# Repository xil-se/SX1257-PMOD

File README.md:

# SX1257 PMOD

This is a PMOD built around the SX1257 transceiver. It uses an I2C-SPI bridge (SC18IS602B) since only 8 io pins are used.

RevA Pin-out:
- 1: I2C SCL
- 2: I2C SDA
- 3: CLK_IN (32 or 36 MHz)
- 4: CLK_OUT (36 MHz)
- 5: I_IN
- 6: Q_IN
- 7: Q_OUT
- 8: I_OUT

## RevA errata
- Change crystal footprint.
- Add 2k pull-ups on i2c scl and sda.
- Maybe swap pin 7 and 8, makese sense to keep in and out symmetric.

# RevB

RevB Pin-out:
- 1: I_IN
- 2: Q_IN
- 3: Q_OUT
- 4: I_OUT
- 5: I2C SCL
- 6: I2C SDA
- 7: CLK_IN (32 or 36 MHz)
- 8: CLK_OUT (36 MHz)

## RevB errata

The pins VR_PA, VR_DIG, VR_ANA1 and VR_ANA2 should *not* be tied to VBAT/VCC, which they are. These are pins for decoupling for the internal voltage regulators, i.e. they should *only* be connected to single decoupling capacitors as stated in the datasheet.

- VR_PA: 10nF
- VR_DIG: 100nF
- VR_ANA1: 100nF
- VR_ANA2: 100nF

RX performance is poor. Why? Maybe related to the above, or bad matching circuit?

In the build of 10 units, 2 failed completely and 2 had very bad RX performance. Maybe related to the issue above.

## Changes for RevC / TODO:

- [x] Fix SX1257 Vreg decoupling issue. Done in [#1][i1] / 176024d
- [x] Change to 0402 components. Done in [#1][i1] / 176024d
- [x] Add optional SI514 I2C-programmable oscillator.

[i1]: https://github.com/xil-se/SX1257-PMOD/pull/1

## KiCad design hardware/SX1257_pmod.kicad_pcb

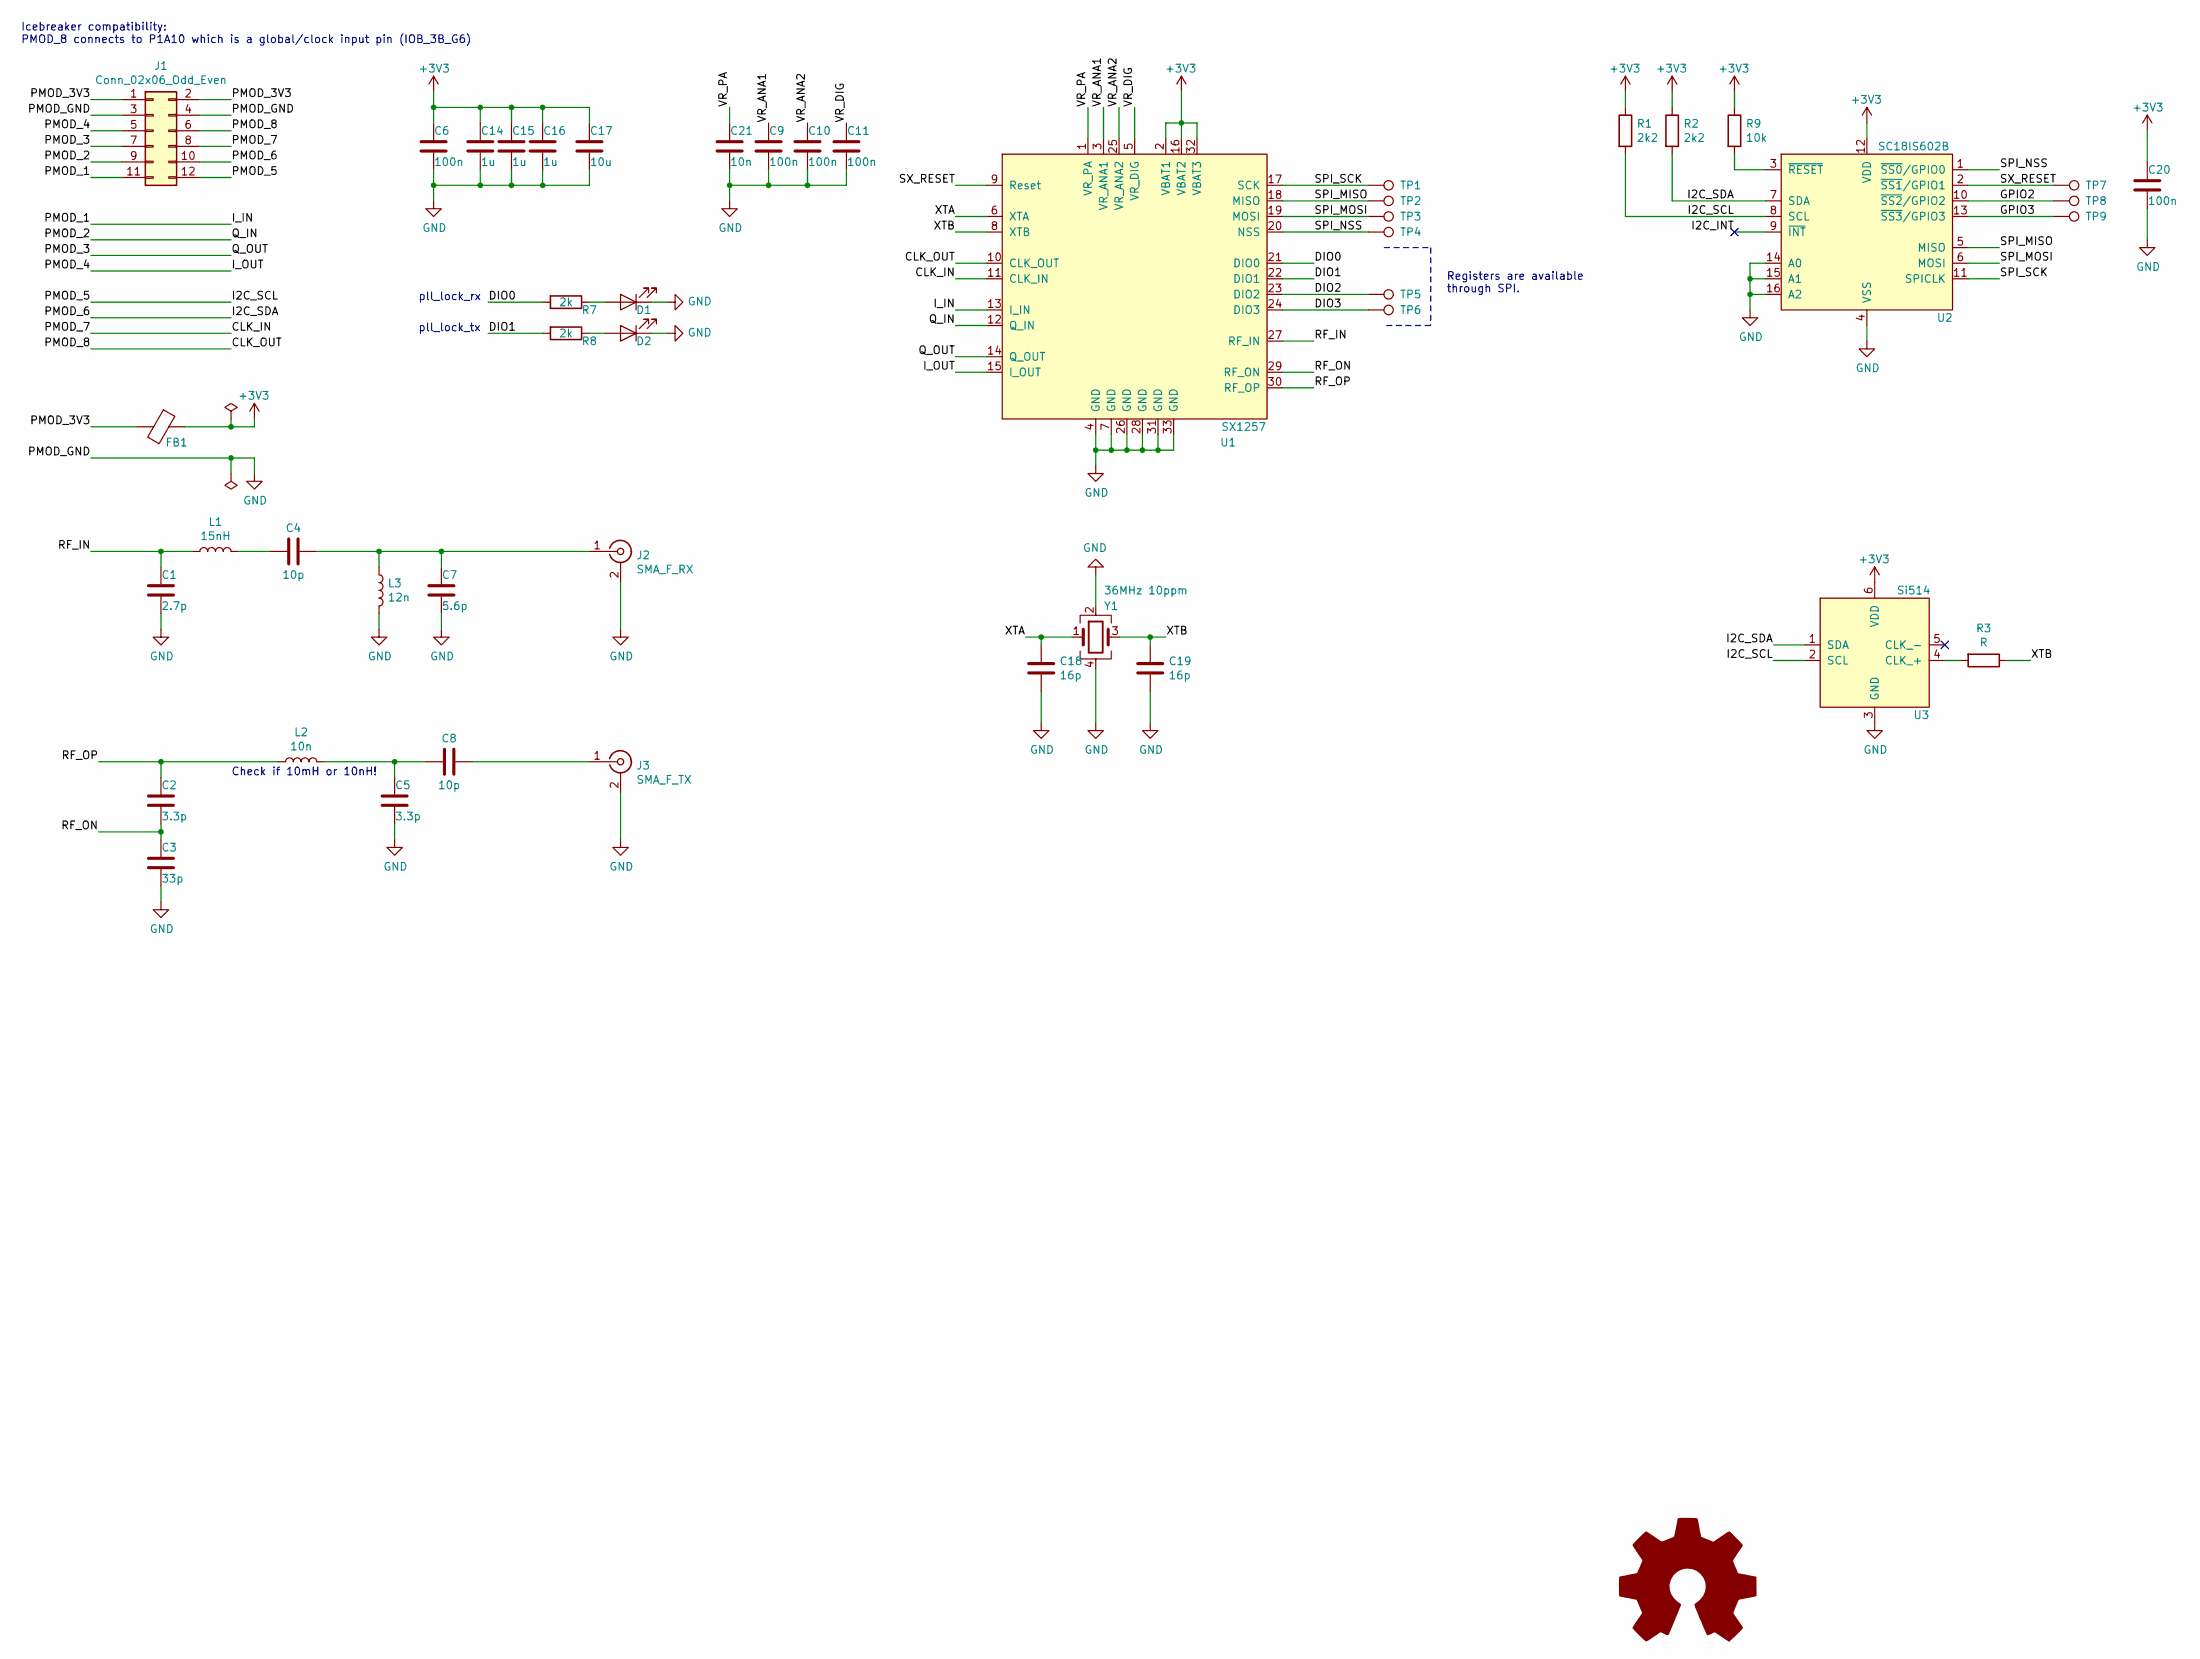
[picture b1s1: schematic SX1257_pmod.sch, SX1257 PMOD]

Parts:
C1: 2.7p; C_0402_1005Metric
C2, C5: 3.3p; C_0402_1005Metric
C3: 33p; C_0402_1005Metric
C4, C8: 10p; C_0402_1005Metric
C6, C9, C10, C11, C20: 100n; C_0402_1005Metric
C7: 5.6p; C_0402_1005Metric
C14, C15, C16: 1u; C_0402_1005Metric
C17: 10u; C_0603_1608Metric
C18, C19: 16p; C_0402_1005Metric
C21: 10n; C_0402_1005Metric
D1, D2: LED; LED_0603_1608Metric
FB1: Ferrite_Bead; L_0603_1608Metric
J1: Conn_02x06_Odd_Even; PinHeader_2x06_P2.54mm_Horizontal
J2: SMA_F_RX; CON-SMA-EDGE; Mouser 960-EMPCB.SMAFSTJBHT
J3: SMA_F_TX; CON-SMA-EDGE; Mouser 960-EMPCB.SMAFSTJBHT
L1: 15nH; L_0402_1005Metric
L2: 10n; L_0402_1005Metric
L3: 12n; L_0402_1005Metric
LOGO1: Logo_Open_Hardware_Large; oshw_logo
R1, R2: 2k2; R_0402_1005Metric
R3: R; R_0402_1005Metric
R7, R8: 2k; R_0402_1005Metric
R9: 10k; R_0402_1005Metric
TP1, TP2, TP3, TP4, TP5, TP6, TP7, TP8, TP9: TestPoint; TestPoint_Pad_D1.0mm
U1: SX1257; QFN-32-1EP_5x5mm_P0.5mm_EP3.1x3.1mm_ThermalVias
U2: SC18IS602B; TSSOP-16_4.4x5mm_P0.65mm
U3: Si514; Oscillator_SMD_Silicon_Labs_3.2x5.0mm_P1.27mm-6pin_5.0x3.2mm
Y1: 36MHz 10ppm; Crystal_SMD_1612-4Pin_1.6x1.2mm; Mouser 815-12W36-6B1UT

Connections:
+3V3: C6.1, C14.1, C15.1, C16.1, C17.1, C20.1, FB1.1, R1.1, R2.1, R9.1, U1.2 (VBAT1), U1.16 (VBAT2), U1.32 (VBAT3), U2.12 (VDD), U3.6 (VDD)
/CLK_IN: J1.8, U1.11 (CLK_IN)
/CLK_OUT: J1.6, U1.10 (CLK_OUT)
/DIO0: R7.2, U1.21 (DIO0)
/DIO1: R8.2, U1.22 (DIO1)
/DIO2: TP5.1, U1.23 (DIO2)
/DIO3: TP6.1, U1.24 (DIO3)
/GPIO2: TP8.1, U2.10 (~SS2~/GPIO2)
/GPIO3: TP9.1, U2.13 (~SS3~/GPIO3)
/I2C_INT: U2.9 (~INT~)
/I2C_SCL: J1.12, R1.2, U2.8 (SCL), U3.2 (SCL)
/I2C_SDA: J1.10, R2.2, U2.7 (SDA), U3.1 (SDA)
/I_IN: J1.11, U1.13 (I_IN)
/I_OUT: J1.5, U1.15 (I_OUT)
/PMOD_2: J1.9, U1.12 (Q_IN)
/PMOD_3: J1.7, U1.14 (Q_OUT)
/PMOD_3V3: FB1.2, J1.1, J1.2
/RF_IN: C1.1, L1.1, U1.27 (RF_IN)
/RF_ON: C2.2, C3.1, U1.29 (RF_ON)
/RF_OP: C2.1, L2.1, U1.30 (RF_OP)
/SPI_MISO: TP2.1, U1.18 (MISO), U2.5 (MISO)
/SPI_MOSI: TP3.1, U1.19 (MOSI), U2.6 (MOSI)
/SPI_NSS: TP4.1, U1.20 (NSS), U2.1 (~SS0~/GPIO0)
/SPI_SCK: TP1.1, U1.17 (SCK), U2.11 (SPICLK)
/SX_RESET: TP7.1, U1.9 (Reset), U2.2 (~SS1~/GPIO1)
/VR_ANA1: C9.1, U1.3 (VR_ANA1)
/VR_ANA2: C10.1, U1.25 (VR_ANA2)
/VR_DIG: C11.1, U1.5 (VR_DIG)
/VR_PA: C21.1, U1.1 (VR_PA)
/XTA: C18.1, U1.6 (XTA), Y1.1
/XTB: C19.1, R3.1, U1.8 (XTB), Y1.3
GND: C1.2, C3.2, C5.2, C6.2, C7.2, C9.2, C10.2, C11.2, C14.2, C15.2, C16.2, C17.2, C18.2, C19.2, C20.2, C21.2, D1.1 (K), D2.1 (K), J1.3, J1.4, J2.2 (Ext), J3.2 (Ext), L3.2, U1.4 (GND), U1.7 (GND), U1.26 (GND), U1.28 (GND), U1.31 (GND), U1.33 (GND), U2.4 (VSS), U2.14 (A0), U2.15 (A1), U2.16 (A2), U3.3 (GND), Y1.2, Y1.4
unnamed: C4.1, C7.1, J2.1 (In), L3.1
unnamed: C4.2, L1.2
unnamed: C5.1, C8.2, L2.2
unnamed: C8.1, J3.1 (In)
unnamed: D1.2 (A), R7.1
unnamed: D2.2 (A), R8.1
unnamed: R3.2, U3.4 (CLK_+)
unnamed: R9.2, U2.3 (~RESET~)

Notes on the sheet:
Check if 10mH or 10nH!
Registers are available through SPI.
Icebreaker compatibility: PMOD_8 connects to P1A10 which is a global/clock input pin (IOB_3B_G6)
pll_lock_rx
pll_lock_tx

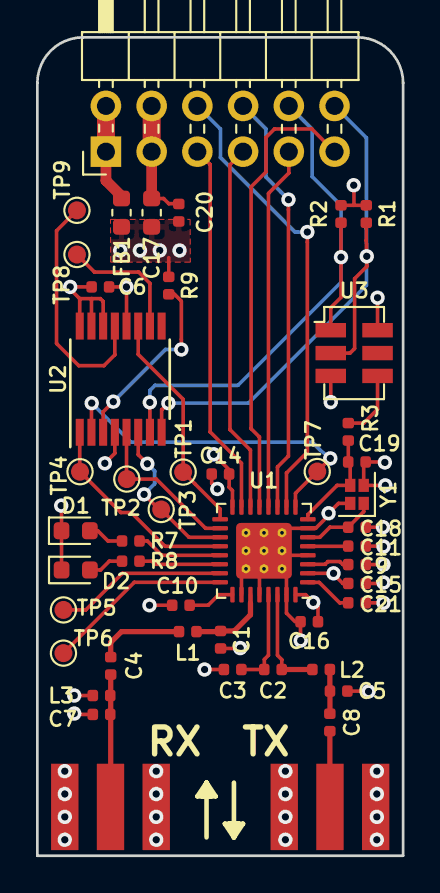
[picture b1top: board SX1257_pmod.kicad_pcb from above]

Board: 4 copper layers, 20.3 x 45.5 mm, 48 parts (1 on the bottom side), 39 nets.

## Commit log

2018-12-31 Initial kicad project
2018-12-31 Add schematic symbol
2019-01-03 Added some caps etc
2019-01-04 Finalized the schematic
2019-01-04 Remove CLK_OUT 0R and tidy up a bit.
2019-01-04 Fix incorrect value of C11 33p => 3.3p
2019-01-04 Change clock
2019-01-04 Add datasheet
2019-01-04 Initial PCB routing
2019-01-05 Fix typo
2019-01-05 Some improvements and pcb work
    - Connected gpio1 to SX_RESET
    - Removed R0 for CLK select
2019-01-05 New pdf
2019-01-06 PCB design almost done.
2019-01-06 Final touches of the pcb
2019-01-06 RevA: Minor changes and produce gerbers
    - Moved the SMA connectors closed to the edges
    - Added silk on the back
2019-01-15 Add souring info about SMA connector
2019-01-21 ibom
2019-01-26 stm32f0 project to talk i2c
2019-01-26 First stab
2019-01-26 Add SC18IS602B driver
2019-01-26 Cleaned up a bit
2019-01-26 sx1257 initial steps
2019-01-26 Frequency hop test
2019-01-26 400kHz and some experiments
2019-01-27 Add readme
2019-03-02 Swap pmod rows and add pull-ups.
2019-03-02 Add gitignore
2019-03-02 Add I2C level shifter
2019-03-02 datasheets
2019-05-07 RevB improvements
    - Clean up routing and improve ground plane
    - Change crystal to 1.6x1.2mm
    - Minor improvements everywhere
2019-05-07 Add gerbers for RevB
2019-05-17 Update ibom to RevB
2019-05-18 RX nasty hack
2019-05-18 gitignore
2019-05-18 Hack, hack
2019-06-08 Update readme with RevB updates
2020-01-01 Relative path for SC18IS602B.lib
2020-01-01 SX1257 symbol: Set VR_* pins to power ouput
2020-01-01 Fix VR_* pins & change most passives to 0402
    This fixes the power pin wiring as mentioned in the RevB errata:
    SX1257 VR_* pins are now only connected to decoupling caps.
    This also moves a lot of caps away from the PMOD header & closer to
    the appropriate power pins.
    Space was getting tight, so this also changes small caps & inductors
    to 0402. As a result, there's also a bit of re-routing to reconnect things.
2020-01-01 Better .gitignore & delete unneeded files
2020-01-01 Change C21 (VR_PA) to 10n
2020-01-01 Add DS40001827A - Microchip LoRa Technology User's Guide
    This has an example schematic for the SX1257 that is much clearer than
    the screenshots in the SX1257 datasheet.
2020-01-01 Update README RevC TODO list
2020-01-02 Remaining passives to 0402 & re-layout to tidy I/Q/CLK
2020-01-02 Adjust RF tracks for JLC 7268 stackup
2020-01-02 Switch to solid GND fill
2020-01-02 Move C6 over to fix DRC error
2020-01-02 Tidy up silk references
2020-01-02 Add Si514 symbol
2020-01-03 Add SiLabs 3.2x5.0mm footprint (for SI514)
2020-01-03 Integrate SI514
2020-01-03 Update README with latest RevC progress
2020-01-03 Fix resistors that accidentally reverted to 0603
2020-01-03 Make SC18IS602B address pins accessible in case of rework
2020-01-03 Update silkscreen with new url and revision
2020-01-03 Show some hidden refrences & minor silk changes
2020-01-03 Si514 datasheet
2020-01-04 Add missing paste layer on Si514 footprint
2020-01-04 RevC
